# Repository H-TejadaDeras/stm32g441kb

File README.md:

# stm32g441kb
STM32G441KB KiCAD Symbol, Footprint, and Development Board for Olin Electric Motorsports

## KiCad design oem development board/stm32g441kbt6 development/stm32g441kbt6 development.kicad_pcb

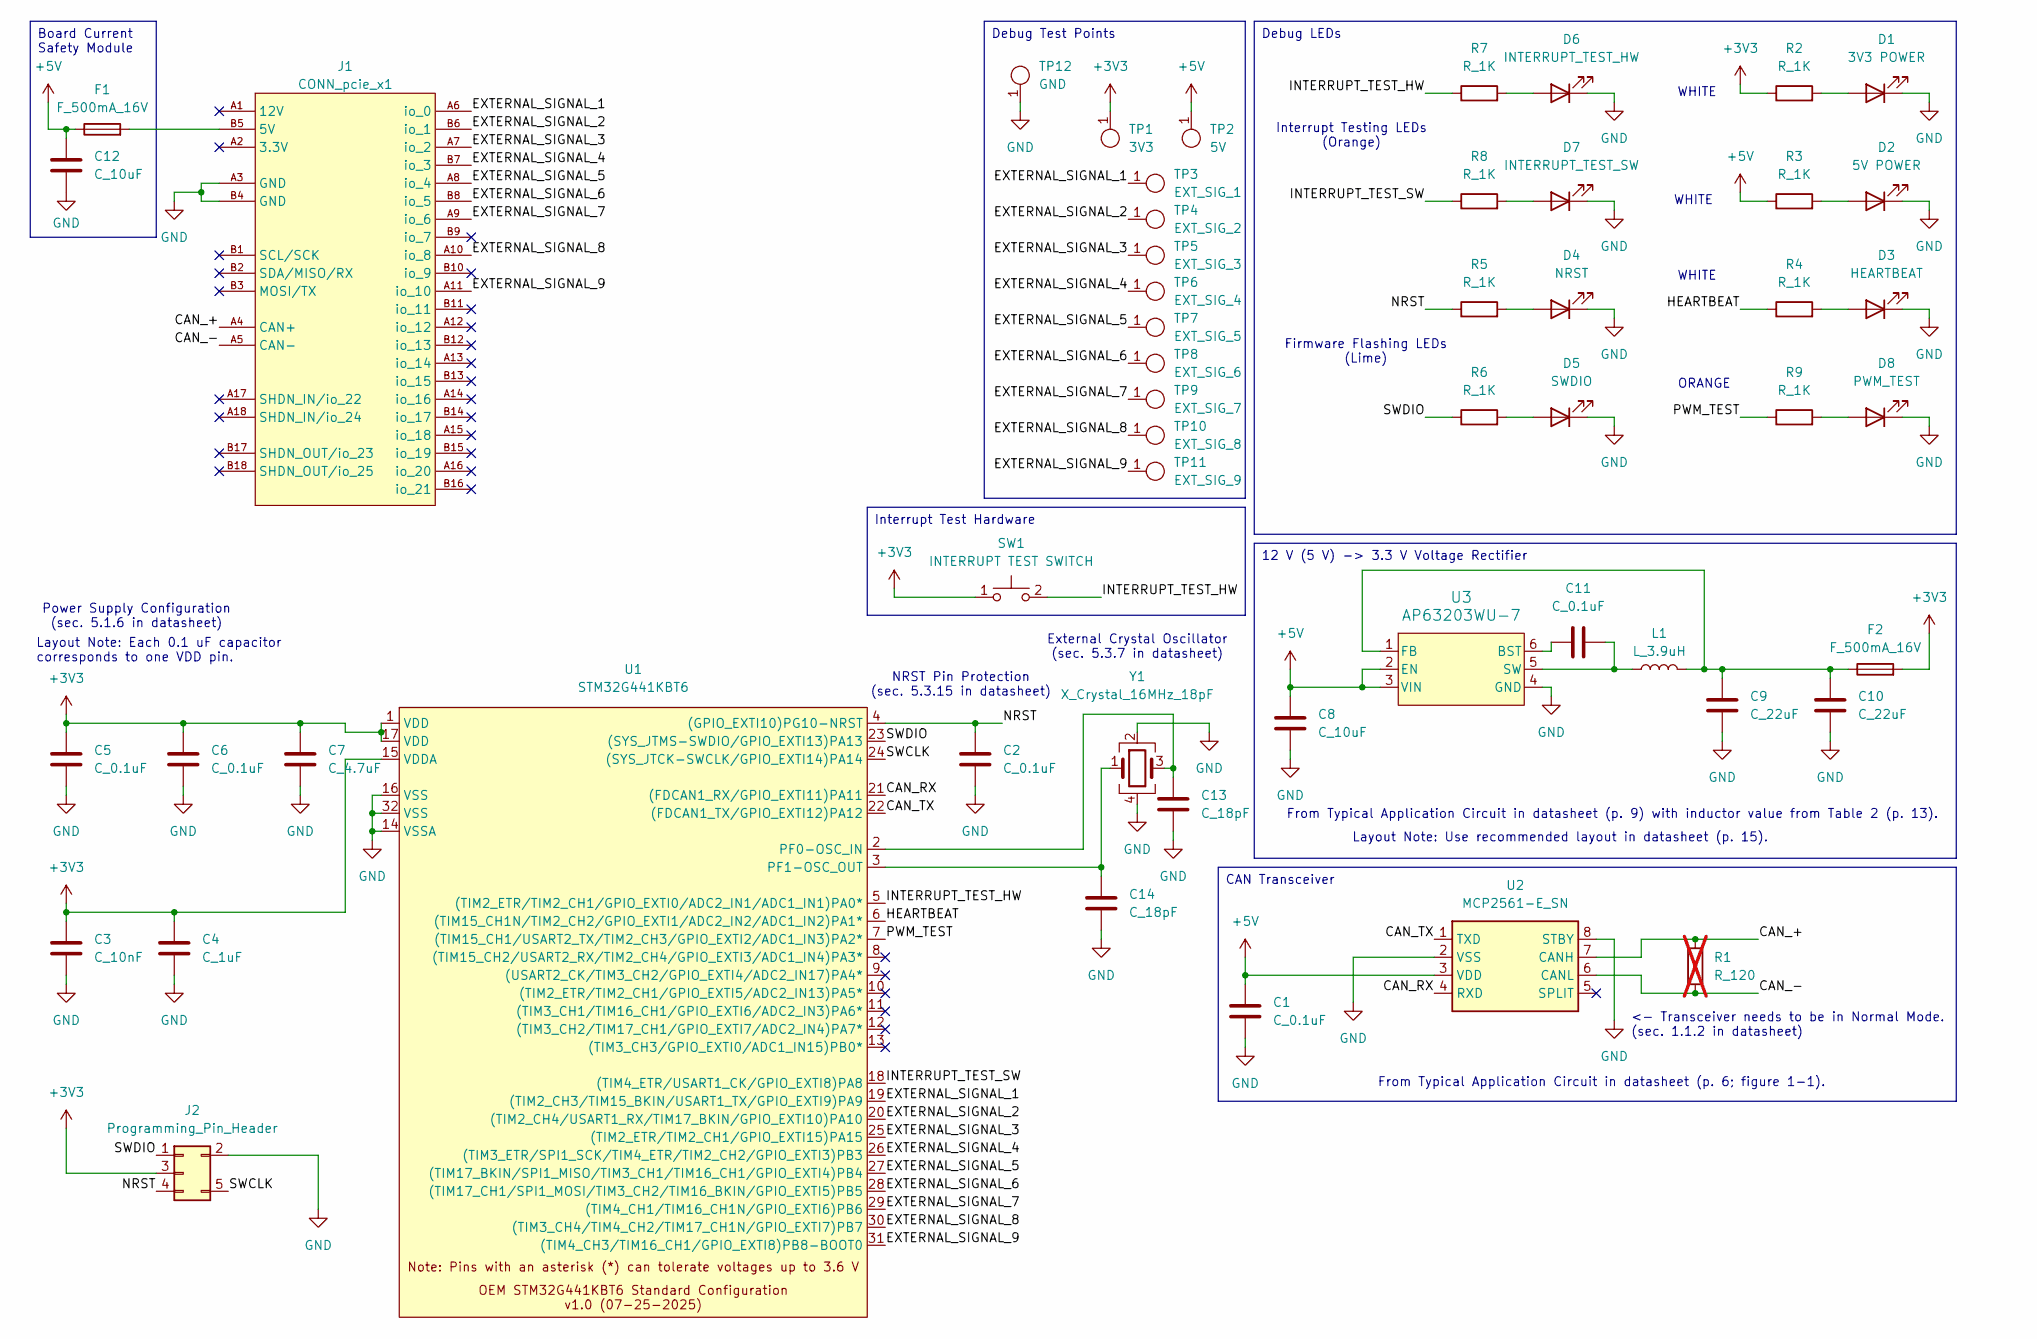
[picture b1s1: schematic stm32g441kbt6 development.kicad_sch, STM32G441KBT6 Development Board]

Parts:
C1, C2, C5, C6, C11: C_0.1uF; C_0603; MPN CL10B104KB8NNWC
C3: C_10nF; C_0603; MPN CL10B103KB8NNNC
C4: C_1uF; C_0603; MPN CL10B105KA8NNNC
C7: C_4.7uF; C_0603; MPN GRT188R61E475ME13D
C8, C12: C_10uF; C_0603; MPN LMK107BBJ106KALT
C9, C10: C_22uF; C_1206_3216Metric; MPN CL31A226KAHNNNE
C13, C14: C_18pF; C_0805_2012Metric; MPN 0603N180J500CT
D1: 3V3 POWER; CHIPLED_0805; MPN B1701TW--20P000314U1930
D2: 5V POWER; CHIPLED_0805; MPN B1701TW--20P000314U1930
D3: HEARTBEAT; CHIPLED_0805; MPN B1701TW--20P000314U1930
D4: NRST; CHIPLED_0805
D5: SWDIO; CHIPLED_0805
D6: INTERRUPT_TEST_HW; CHIPLED_0805
D7: INTERRUPT_TEST_SW; CHIPLED_0805
D8: PWM_TEST; CHIPLED_0805
F1, F2: F_500mA_16V; Fuse_1210; MPN 0ZCH0050FF2G
J1: CONN_pcie_x1; pcie_x1
J2: Programming_Pin_Header; Programming_Pin_Header_Keyed
L1: L_3.9uH; IND_BOURNS_SRR5018
R1: R_120; R_0603; MPN RC0603FR-13120RL; not fitted
R2, R3, R4, R5, R6, R7, R8, R9: R_1K; R_0603; MPN RMCF0603FT1K00
SW1: INTERRUPT TEST SWITCH; SW_B3U-1000P_4.2x1.7mm; MPN B3U-1000P
TP1: 3V3; Test_Point_SMD; MPN 5019
TP2: 5V; Test_Point_SMD; MPN 5019
TP3: EXT_SIG_1; Test_Point_SMD; MPN 5019
TP4: EXT_SIG_2; Test_Point_SMD; MPN 5019
TP5: EXT_SIG_3; Test_Point_SMD; MPN 5019
TP6: EXT_SIG_4; Test_Point_SMD; MPN 5019
TP7: EXT_SIG_5; Test_Point_SMD; MPN 5019
TP8: EXT_SIG_6; Test_Point_SMD; MPN 5019
TP9: EXT_SIG_7; Test_Point_SMD; MPN 5019
TP10: EXT_SIG_8; Test_Point_SMD; MPN 5019
TP11: EXT_SIG_9; Test_Point_SMD; MPN 5019
TP12: GND; Test_Point_SMD; MPN 5019
U1: STM32G441KBT6
U2: MCP2561-E_SN; SOIC127P600X175-8N; Mouser Part Number 579-MCP2561-E/SN
U3: AP63203WU-7; AP63203WU-7_DIO
Y1: X_Crystal_16MHz_18pF; Crystal_TXC7M; MPN 7M-16.000MAAJ-T

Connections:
+3V3: C3.1, C4.1, C5.1, C6.1, C7.1, F2.2, J2.3, R2.1, SW1.1, TP1.1, U1.1 (VDD), U1.15 (VDDA), U1.17 (VDD)
+5V: C1.2, C8.1, C12.1, F1.1, R3.1, TP2.1, U2.3 (VDD), U3.2 (EN), U3.3 (VIN)
/CAN_+: J1.A4 (CAN+), R1.1, U2.7 (CANH)
/CAN_-: J1.A5 (CAN-), R1.2, U2.6 (CANL)
/CAN_RX: U1.21 ((FDCAN1_RX/GPIO_EXTI11)PA11), U2.4 (RXD)
/CAN_TX: U1.22 ((FDCAN1_TX/GPIO_EXTI12)PA12), U2.1 (TXD)
/EXTERNAL_SIGNAL_1: J1.A6 (io_0), TP3.1, U1.19 ((TIM2_CH3/TIM15_BKIN/USART1_TX/GPIO_EXT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)
/EXTERNAL_SIGNAL_2: J1.B6 (io_1), TP4.1, U1.20 ((TIM2_CH4/USART1_RX/TIM17_BKIN/GPIO_EXT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)
/EXTERNAL_SIGNAL_3: J1.A7 (io_2), TP5.1, U1.25 ((TIM2_ETR/TIM2_CH1/GPIO_EXTI15)PA15)
/EXTERNAL_SIGNAL_4: J1.B7 (io_3), TP6.1, U1.26 ((TIM3_ETR/SPI1_SCK/TIM4_ETR/TIM2_CH2/GP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)
/EXTERNAL_SIGNAL_5: J1.A8 (io_4), TP7.1, U1.27 ((TIM17_BKIN/SPI1_MISO/TIM3_CH1/TIM16_CH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)
/EXTERNAL_SIGNAL_6: J1.B8 (io_5), TP8.1, U1.28 ((TIM17_CH1/SPI1_MOSI/TIM3_CH2/TIM16_BKI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)
/EXTERNAL_SIGNAL_7: J1.A9 (io_6), TP9.1, U1.29 ((TIM4_CH1/TIM16_CH1N/GPIO_EXTI6)PB6)
/EXTERNAL_SIGNAL_8: J1.A10 (io_8), TP10.1, U1.30 ((TIM3_CH4/TIM4_CH2/TIM17_CH1N/GPIO_EXTI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)
/EXTERNAL_SIGNAL_9: J1.A11 (io_10), TP11.1, U1.31 ((TIM4_CH3/TIM16_CH1/GPIO_EXTI8)PB8-BOOT0)
/HEARTBEAT: R4.1, U1.6 ((TIM15_CH1N/TIM2_CH2/GPIO_EXTI1/ADC2_IN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)
/INTERRUPT_TEST_HW: R7.1, SW1.2, U1.5 ((TIM2_ETR/TIM2_CH1/GPIO_EXTI0/ADC2_IN1/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)
/INTERRUPT_TEST_SW: R8.1, U1.18 ((TIM4_ETR/USART1_CK/GPIO_EXTI8)PA8)
/NRST: C2.1, J2.4, R5.1, U1.4 ((GPIO_EXTI10)PG10-NRST)
/PWM_TEST: R9.1, U1.7 ((TIM15_CH1/USART2_TX/TIM2_CH3/GPIO_EXTI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)
/SWCLK: J2.5, U1.24 ((SYS_JTCK-SWCLK/GPIO_EXTI14)PA14)
/SWDIO: J2.1, R6.1, U1.23 ((SYS_JTMS-SWDIO/GPIO_EXTI13)PA13)
GND: C1.1, C2.2, C3.2, C4.2, C5.2, C6.2, C7.2, C8.2, C9.2, C10.2, C12.2, C13.2, C14.2, D1.1 (K), D2.1 (K), D3.1 (K), D4.1 (K), D5.1 (K), D6.1 (K), D7.1 (K), D8.1 (K), J1.A3 (GND), J1.B4 (GND), J2.2, TP12.1, U1.14 (VSSA), U1.16 (VSS), U1.32 (VSS), U2.2 (VSS), U2.8 (STBY), U3.4 (GND), Y1.2, Y1.4
unnamed: D1.2 (A), R2.2
unnamed: D2.2 (A), R3.2
unnamed: D3.2 (A), R4.2
unnamed: D4.2 (A), R5.2
unnamed: D5.2 (A), R6.2
unnamed: D6.2 (A), R7.2
unnamed: D7.2 (A), R8.2
unnamed: D8.2 (A), R9.2
unnamed: F1.2, J1.B5 (5V)
unnamed: C13.1, U1.2 (PF0-OSC_IN), Y1.3
unnamed: C14.1, U1.3 (PF1-OSC_OUT), Y1.1
unnamed: C11.1, U3.6 (BST)
unnamed: C9.1, C10.1, F2.1, L1.2, U3.1 (FB)
unnamed: C11.2, L1.1, U3.5 (SW)

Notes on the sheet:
WHITE
Layout Note: Use recommended layout in datasheet (p. 15).
<- Transceiver needs to be in Normal Mode. (sec. 1.1.2 in datasheet)
Interrupt Testing LEDs (Orange)
From Typical Application Circuit in datasheet (p. 6; figure 1-1).
NRST Pin Protection (sec. 5.3.15 in datasheet)
Power Supply Configuration (sec. 5.1.6 in datasheet)
ORANGE
External Crystal Oscillator (sec. 5.3.7 in datasheet)
Layout Note: Each 0.1 uF capacitor corresponds to one VDD pin.
Firmware Flashing LEDs (Lime)
From Typical Application Circuit in datasheet (p. 9) with inductor value from Table 2 (p. 13).
12 V (5 V) -> 3.3 V Voltage Rectifier
Debug LEDs
Interrupt Test Hardware
Debug Test Points
Board Current Safety Module
CAN Transceiver

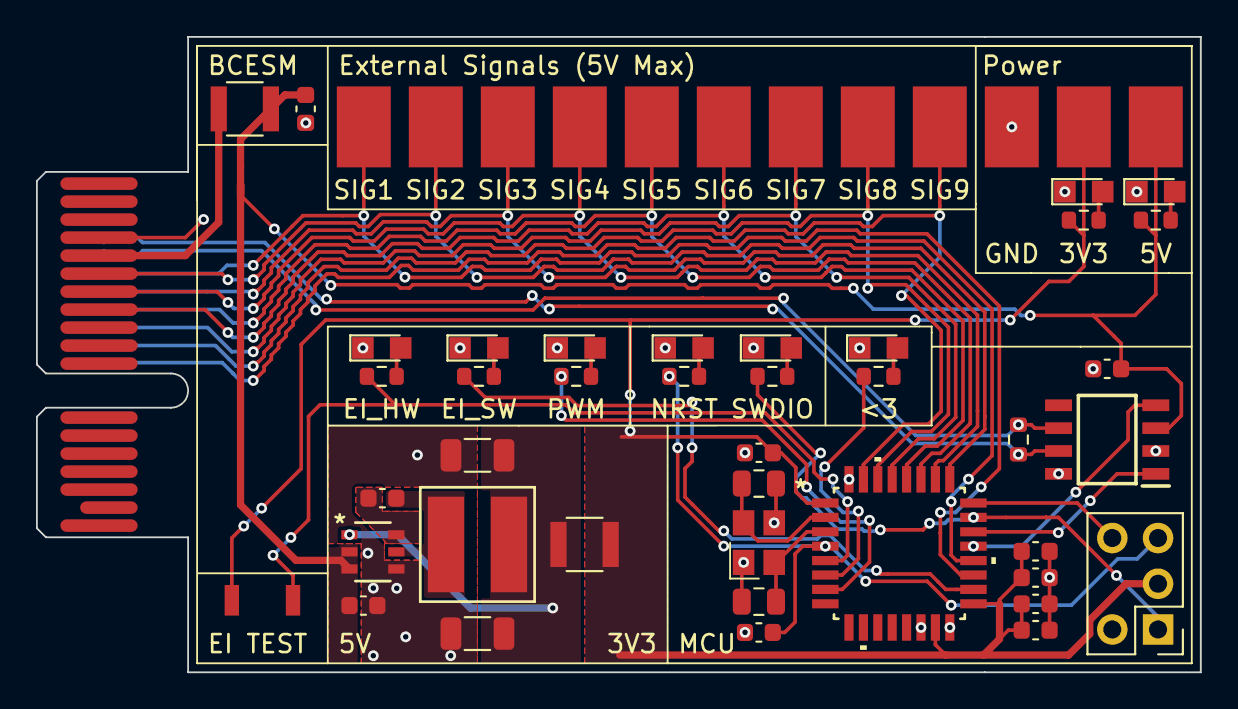
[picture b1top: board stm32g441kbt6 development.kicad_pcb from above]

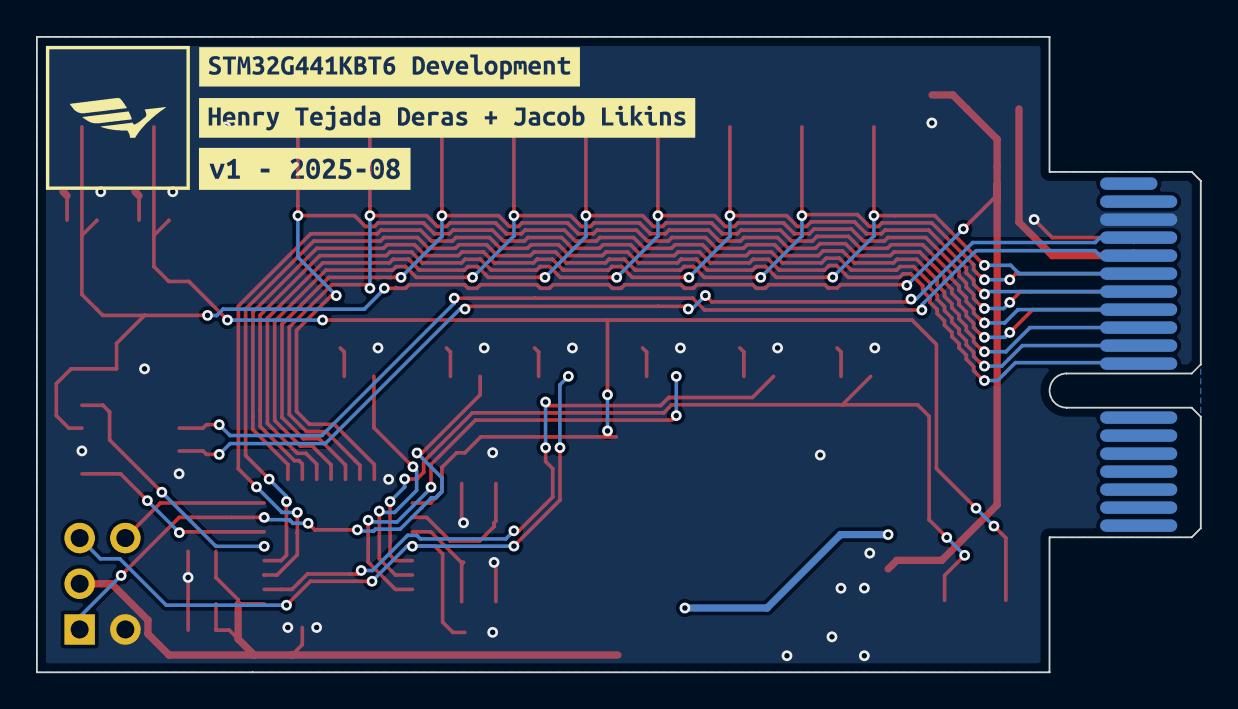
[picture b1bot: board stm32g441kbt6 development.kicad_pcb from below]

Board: 2 copper layers, 64.7 x 35.3 mm, 56 parts (3 on the bottom side), 37 nets.

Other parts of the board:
kibuzzard-68A62DAB: G***; kibuzzard-68A62DAB
kibuzzard-68A62DD1: G***; kibuzzard-68A62DD1
kibuzzard-68A62E54: G***; kibuzzard-68A62E54

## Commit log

2025-07-24 Add Datasheet and Pinout for STM32G441KBT6; Started KiCAD Symbol
2025-07-24 Added ADC and GPIO pinouts
2025-07-26 Added Pin Definitions and Created Pin Categories
2025-07-26 Added Footprint; Small Symbol Adjustments
2025-07-27 Created Simplified General Use Symbol
2025-07-27 Minor Visual Changes to Symbols, Removed Basic and Advanced Timers from Simplified Pinout
2025-07-27 Adjusted symbol box to match between regular and detailed symbols.
2025-07-27 Fixed configuration issue with symbol attributes (symbol was omitted from BOM and things)
2025-07-31 Seperated Power -> 3.3 V and GND in symbols.
2025-08-14 Added Keyed Programming Pin Header, LDO Voltage Regulator, and reference manual
2025-08-14 Added Debug LEDs, Some Test Points, Minor changes to STM32G441KBT6 symbol
2025-08-16 Condensed Symbol Design; Slight changes to development board
2025-08-16 Added footprints for new voltage regulator components, added test points and other things
2025-08-19 Added 3D Models, Started PCB Design, Minor Fixes to Schematics
2025-08-19 Finished PCB Design
2025-08-20 Added Datasheet References, Minor PCB Design Changes
2025-08-20 Added Minor PCB Cosmetic and Schematic Things
2025-08-20 Added Fab Files for PCB
2025-08-20 Added Fab Files for PCB with Rounded Corners
2025-08-21 Changed Crystal Oscillator Load Capacitors to 30 pF from 18 pF (this should provide the manufacturer's specified load capacitance)
